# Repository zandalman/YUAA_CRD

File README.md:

## YUAA CRD

### Purpose
Our goal is to develop a cosmic ray detector (CRD) to serve as the scientific payload for the Yale Undergraduate Aerospace Association (YUAA) CubeSat. We will use cosmic rays to map the boundaries of the South Atlantic Anomaly (SAA).

### General CubeSat Info

CubeSats are miniature satellites composed of units consisting of 10 cm cubes. Yale was chosen by NASA as one of sixteen schools across the country whose CubeSat will be launched into space as auxiliary payloads on NASA missions. The Yale CubeSat consists of two 10 cm cube units. The CubeSat team is divided into several subteams: attitude determination and control (ADCS), radio, software, and cosmic ray detector (CRD). The CRD team interacts significantly with the ADCS and software teams. The software team writes C programs for our I2C components. We work with the ADCS team to coordinate mechanical design in the CubeSat, which is necessary due to the size constraints. The bulkiest part of the ADCS system is the gravity gradient boom (GGB), a measuring tape which spools out of the bottom of the CubeSat to generate restoring torques which stabilize the CubeSat’s orientation. The GGB includes a rotary encoder which provides feedback on the length of the GGB. The ADCS system also includes magnetorquers, electromagnets which generate torques using the Earth’s magnetic field, to maneuver the CubeSat.

### Background

#### Cosmic Rays

Cosmic rays are high-energy radiation originating from outside the solar system. About 99% of cosmic rays are bare atomic nuclei. 90% of these nuclei are protons (hydrogen nuclei), 9% are alpha particles (helium nuclei), and 1% are heavier elements. The other 1% of cosmic rays are beta particles (solitary electrons). Cosmic rays also include trace amounts of antiparticles like positrons and antiprotons. Sometimes, gamma rays (high-energy photons) are also considered cosmic rays. When cosmic rays enter the Earth’s atmosphere, they collide with atoms and molecules, producing a cascade of lighter particles known as secondary cosmic rays. Secondary cosmic rays are typically composed of neutrons, pions, kaons, and their antiparticles. Pions and kaons quickly decay into muons, neutrinos, and their antiparticles, which can be detected on Earth’s surface. The muon lifetime of 2.2 us should not be enough for muons to reach the surface of Earth, but due to relativistic time dilation their effective lifetime is longer in our reference frame. 1 Muons have similar properties to electrons but about 200 times the mass. Because muons are charged particles, we can use muons to test our detection circuitry before sending it into space.

#### Earth’s Magnetic Field

The Earth has a dipolar magnetic field generated by convection currents in Earth’s molten iron and nickel outer core. Energetic charged particles originating from solar wind and cosmic rays are captured by Earth’s magnetic field. Charged particles in a magnetic field move in helices about magnetic field lines. The concentration of charged particles peaks in two distinct regions above Earth’s surface, known as the inner and outer Van Allen belts. The gap between the Van Allen belts is caused by low frequency radio waves whose origin is still an area of active
research. 

There is a nonzero angle between the axis of Earth’s dipole magnetic field and its axis of rotation, causing the inner Van Allen belt to make its closest approach of about 2000 km to Earth’s surface above the South Atlantic. This region of enhanced radiation is called the South Atlantic Anomaly (SAA). The SAA dips low enough to intersect low Earth orbit. Satellites passing through the SAA are exposed to elevated levels of radiation for minutes at a time, leading to malfunctions, loss of observational time for telescopes, and danger to astronauts in the ISS.

#### Scintillators

A scintillator is a material that emits photons when excited by ionizing radiation. Commonly used scintillators often emit photons in the optical bands. There are many types of scintillators including organic crystals, organic liquids, plastic scintillators, inorganic crystals, gaseous scintillators, glasses, and perovskites. We use plastic scintillators, in which the primary fluorescent emitter, or fluor, is suspended in a base.

### Design

#### Mechanical

Using a band saw and a mill, we cut the scintillator down to a 1 cm cube due to size constraints in the CubeSat. Within the SAA, the particle flux is so high that our detection events would overlap. A layer of aluminum shielding around the scintillator reduces the number of events to the order of ~100 events per second. We calculated that a shielding thickness of 7 mm is sufficient. Because protons are more massive than electrons, cosmic ray protons typically have more energy than cosmic ray electrons, so the ratio of proton to electron events increases with shielding thickness.

The shielding is a 25 x 25 x 28 mm rectangular prism of aluminum with an 11 x 11 x 14 mm hole in the center for the scintillator cube and the SiPM. For ease of machining, the shielding is composed of 3 sections which are held together by 6-32 screws. At each of the bottom corners, the aluminum extends slightly further to give space for mounting holes.

When a charged particle passes through the scintillator, it deposits its kinetic energy into photons. We coat five sides of the scintillator with a reflective paint so that most photons eventually exit the scintillator at a single face. The non-coated face has a silicon photomultiplier (SiPM) which will detect the photons. The SiPM is optically coupled to the scintillator with optical jelly, an amorphous material with a prescribed refractive index. The SiPM is held fast against the scintillator by rubber stops which push against the inside faces of the shielding.

The SiPM is soldered onto a small printed circuit board (PCB) using a ball grid array (BGA). The PCB contains pads for the anode and cathode. Wires will be soldered directly to these pads and exit the shielding through a hole. The SiPM is AC coupled to a charge-sensitive preamplifier (preamp). The AC coupling circuit and the preamp come from an evaluation kit created by Ketek. The AC coupling circuit is mounted in a Thorlabs mount and the preamp is mounted in a rectangular aluminum box which acts as a Faraday cage, protecting it from radiation.

All of the circuitry minus the AC coupling circuit and preamp are contained on a custom 4-layer PCB, whose irregular shape is determined by the size constraints imposed by the GGB. This custom PCB will connect to the SiPM, AC coupling circuit, and preamp by a combination of wires and micro coax cables. Wires will be twisted together in pairs for extra stability.

#### Electrical

Our custom analog circuitry will count the number of cosmic ray detection events and classify them according to particle type. Our integrated circuit (IC) components communicate with the onboard computer (OBC) using I2C protocol, which requires clock and data lines. We have access to one set of clock and data lines from the OBC. An important aspect of I2C is that two devices cannot use the same clock and data lines if they have the same I2C address. Most IC chips which use I2C have address pins which allow you to set the I2C address to avoid overlap. We also have access to a 5 V power supply from the OBC.

As charged particles pass through the scintillator, their kinetic energy is converted into photons which activate cells on the SiPM. The SiPM is an avalanche photodiode, meaning that it consists of an array of photodiode cells. When a photon hits a cell, the cell emits electrons via the photoelectric effect. There is some “dead time” where the cell cannot detect another photon, so having an array of cells allows the SiPM to detect many photons in quick succession. The output pulse generated by the SiPM from a detection event is a sum of the signals generated by all of the photons produced by the particle passing through the scintillator.

The SiPM is AC coupled to a charge-sensitive preamp. In contrast to DC coupling, AC coupling rejects DC components of the signal, blocking any DC bias or offset voltage. AC coupling becomes important when the pulse frequency is sufficiently high that pulses overlap, resulting in a nonzero offset.

The preamp creates output pulses with an integrated voltage equal to the integrated current (i.e. charge) of the input pulses. The charge of the input pulses is physically meaningful because it is proportional to the total energy of the photons collected by the SiPM. The output pulses from the pre-amp look like a steep rising edge followed by an exponential decay with a time constant of ~100 ns. The height of the pulses ranges from 10 mV to 100 mV depending on the type of particle. Because all pulses have approximately the same shape, we can use the height of the pulse as a proxy for the integrated voltage. This pulse height analysis (PHA) is common in radiation detection.

If we had a larger budget, we would use a commercial multi-channel analyzer (MCA). However, instead we bin pulses by pulse height manually. Each pulse height bin is created with a system of three high-speed comparators. Two comparators act as upper and lower discriminators and a third comparator acts as an AND gate, only outputting high if the input voltage is between the two discriminators. The comparators are contained in IC chips with 4 comparators each. We have 7 bins total, so we need 21 comparators or 6 IC chips. The discriminator levels are set by 8 bit digital-to-analog converters (DACs). The DACs are contained in an IC chip with 8 DACs.

The outputs from the comparators are fed into real time clock (RTC) IC chips, which we program to count the number of pulses over the course of 5 min. There are 8 RTC chips, 7 for the pulse height bins and one for counting pulses from the rotary encoder for the GGB. The RTC chips only have one I2C address bin and therefore only two possible I2C addresses. We use an I2C multiplexer to mediate communication between the OBC and the RTC chips. The multiplexer has one input set of clock and data lines and four output sets of clock and data lines which each are used by 2 RTC chips, one with each possible I2C address.

We only have access to a 5 V power supply from the OBC. However, the preamp requires a 12 V power supply and the AC coupling circuit requires a 30 V bias voltage. We use boost converters to generate these voltages from the 5 V supply. All components draw negligible current, so there is no worry about drawing too much current.

The light output of the scintillator is temperature dependent and we don’t know exactly what the equilibrium temperature will be in the CubeSat once it is in space. Therefore, we use resistor temperature devices (RTDs) to monitor the temperature on our custom PCB and near the shielding.

The code for interfacing between the OBC and the I2C components of the circuit is managed by
the software subteam of the CubeSat and is available upon request.

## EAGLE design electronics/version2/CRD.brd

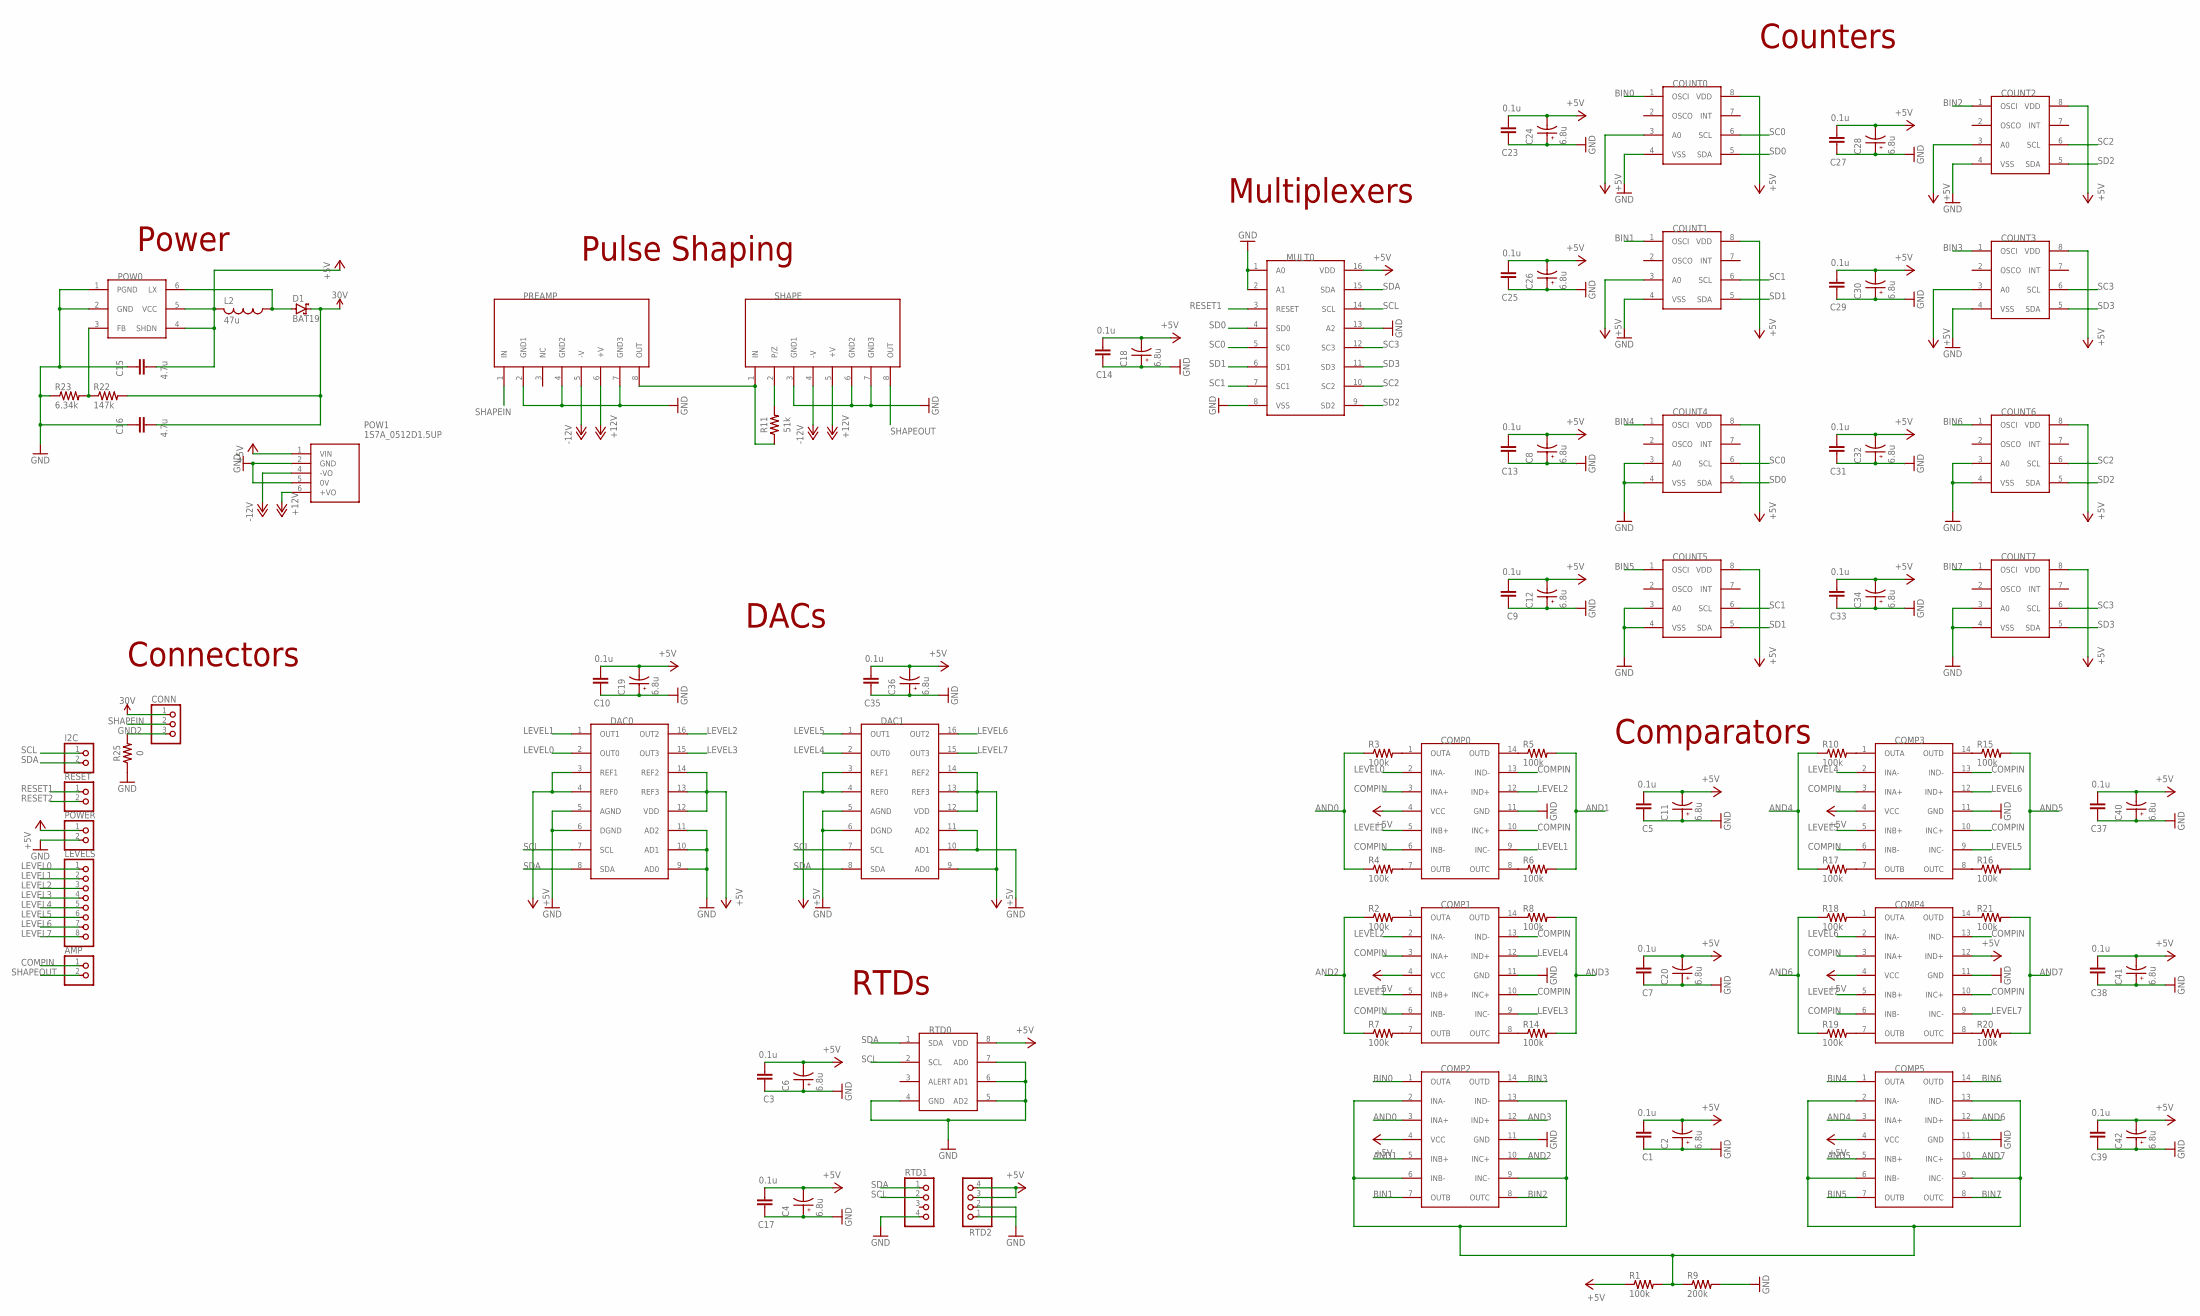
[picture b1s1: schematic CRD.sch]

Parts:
AMP: PINHD-1X2; 1X02
C1, C3, C5, C7, C9, C10, C13, C14, C17, C23, C25, C27, C29, C31, C33, C35, C37, C38, C39: 0.1u; CAP_1206
C2, C4, C6, C8, C11, C12, C18, C19, C20, C24, C26, C28, C30, C32, C34, C36, C40, C41, C42: 6.8u; CAPPRD150W45D400H700
C15, C16: 4.7u; CAP_1206
COMP0, COMP1, COMP2, COMP3, COMP4, COMP5: MAX9108ESD+; SOIC127P600X155-14N
CONN: PINHD-1X3; 1X03
COUNT0, COUNT1, COUNT2, COUNT3, COUNT4, COUNT5, COUNT6, COUNT7: PCF8583; SOIC127P1032X265-8N
D1: BAT19; DO35-10
DAC0, DAC1: MAX520BEWE+; SOIC127P1032X265-16N
I2C: PINHD-1X2; 1X02
L2: 47u; L1812
LEVELS: PINHD-1X8; 1X08
MULT0: PCA9546A; SOIC127P600X175-16N
POW0: MAX5025; SOT95P240X110-6N
POW1: 1S7A_0512D1.5UP; 1S7A_0505D15UP
POWER: PINHD-1X2; 1X02
PREAMP: CR-113; HDRV8W64P254_1X8_1016X508X838B
R1, R2, R3, R4, R5, R6, R7, R8, R10, R14, R15, R16, R17, R18, R19, R20, R21: 100k; RES_1206
R9: 200k; RES_1206
R11: 51k; RESAD1176W63L850D250B
R22: 147k; RES_1206
R23: 6.34k; RES_1206
R25: 0; RESAD724W46L381D178B
RESET: PINHD-1X2; 1X02
RTD0: NCT175DMR2G; SOP65P490X110-8N
RTD1, RTD2: PINHD-1X4; 1X04
SHAPE: CR-200; HDRV8W64P254_1X8_1016X508X838B

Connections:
+5V: C1.2, C2.N, C3.2, C4.N, C5.2, C6.N, C7.2, C8.N, C9.2, C10.2, C11.N, C12.N, C13.2, C14.2, C15.2, C17.2, C18.N, C19.N, C20.N, C23.2, C24.N, C25.2, C26.N, C27.2, C28.N, C29.2, C30.N, C31.2, C32.N, C33.2, C34.N, C35.2, C36.N, C37.2, C38.2, C39.2, C40.N, C41.N, C42.N, COMP0.4 (VCC), COMP1.4 (VCC), COMP2.4 (VCC), COMP3.4 (VCC), COMP4.4 (VCC), COMP4.12 (IND+), COMP5.4 (VCC), COUNT0.3 (A0), COUNT0.8 (VDD), COUNT1.3 (A0), COUNT1.8 (VDD), COUNT2.3 (A0), COUNT2.8 (VDD), COUNT3.3 (A0), COUNT3.8 (VDD), COUNT4.8 (VDD), COUNT5.8 (VDD), COUNT6.8 (VDD), COUNT7.8 (VDD), DAC0.3 (REF1), DAC0.4 (REF0), DAC0.12 (VDD), DAC0.13 (REF3), DAC0.14 (REF2), DAC1.3 (REF1), DAC1.4 (REF0), DAC1.9 (AD0), DAC1.12 (VDD), DAC1.13 (REF3), DAC1.14 (REF2), L2.2, MULT0.16 (VDD), POW0.4 (SHDN), POW0.5 (VCC), POW1.1 (VIN), POWER.1, R1.1, RTD0.8 (VDD), RTD2.3, RTD2.4
+12V: POW1.6 (+VO), PREAMP.6 (+V), SHAPE.5 (+V)
-12V: POW1.4 (-VO), PREAMP.5 (-V), SHAPE.4 (-V)
AND0: COMP2.3 (INA+), R3.1, R4.1
AND1: COMP2.5 (INB+), R5.2, R6.2
AND2: COMP2.10 (INC+), R2.1, R7.1
AND3: COMP2.12 (IND+), R8.2, R14.2
AND4: COMP5.3 (INA+), R10.1, R17.1
AND5: COMP5.5 (INB+), R15.2, R16.2
AND6: COMP5.12 (IND+), R18.1, R19.1
AND7: COMP5.10 (INC+), R20.2, R21.2
BIN0: COMP2.1 (OUTA), COUNT0.1 (OSCI)
BIN1: COMP2.7 (OUTB), COUNT1.1 (OSCI)
BIN2: COMP2.8 (OUTC), COUNT2.1 (OSCI)
BIN3: COMP2.14 (OUTD), COUNT3.1 (OSCI)
BIN4: COMP5.1 (OUTA), COUNT4.1 (OSCI)
BIN5: COMP5.7 (OUTB), COUNT5.1 (OSCI)
BIN6: COMP5.14 (OUTD), COUNT6.1 (OSCI)
BIN7: COMP5.8 (OUTC), COUNT7.1 (OSCI)
COMPIN: AMP.1, COMP0.3 (INA+), COMP0.6 (INB-), COMP0.10 (INC+), COMP0.13 (IND-), COMP1.3 (INA+), COMP1.6 (INB-), COMP1.10 (INC+), COMP1.13 (IND-), COMP3.3 (INA+), COMP3.6 (INB-), COMP3.10 (INC+), COMP3.13 (IND-), COMP4.3 (INA+), COMP4.6 (INB-), COMP4.10 (INC+), COMP4.13 (IND-)
GND: C1.1, C2.P, C3.1, C4.P, C5.1, C6.P, C7.1, C8.P, C9.1, C10.1, C11.P, C12.P, C13.1, C14.1, C15.1, C16.1, C17.1, C18.P, C19.P, C20.P, C23.1, C24.P, C25.1, C26.P, C27.1, C28.P, C29.1, C30.P, C31.1, C32.P, C33.1, C34.P, C35.1, C36.P, C37.1, C38.1, C39.1, C40.P, C41.P, C42.P, COMP0.11 (GND), COMP1.11 (GND), COMP2.11 (GND), COMP3.11 (GND), COMP4.11 (GND), COMP5.11 (GND), COUNT0.4 (VSS), COUNT1.4 (VSS), COUNT2.4 (VSS), COUNT3.4 (VSS), COUNT4.3 (A0), COUNT4.4 (VSS), COUNT5.3 (A0), COUNT5.4 (VSS), COUNT6.3 (A0), COUNT6.4 (VSS), COUNT7.3 (A0), COUNT7.4 (VSS), DAC0.5 (AGND), DAC0.6 (DGND), DAC0.9 (AD0), DAC0.10 (AD1), DAC0.11 (AD2), DAC1.5 (AGND), DAC1.6 (DGND), DAC1.10 (AD1), DAC1.11 (AD2), MULT0.1 (A0), MULT0.2 (A1), MULT0.8 (VSS), MULT0.13 (A2), POW0.1 (PGND), POW0.2 (GND), POW1.2 (GND), POW1.5 (0V), POWER.2, PREAMP.2 (GND1), PREAMP.4 (GND2), PREAMP.7 (GND3), R9.2, R23.1, R25.1, RTD0.4 (GND), RTD0.5 (AD2), RTD0.6 (AD1), RTD0.7 (AD0), RTD1.4, RTD2.2, SHAPE.3 (GND1), SHAPE.6 (GND2), SHAPE.7 (GND3)
GND2: CONN.3, R25.2
LEVEL0: COMP0.2 (INA-), DAC0.2 (OUT0), LEVELS.1
LEVEL1: COMP0.5 (INB+), COMP0.9 (INC-), DAC0.1 (OUT1), LEVELS.2
LEVEL2: COMP0.12 (IND+), COMP1.2 (INA-), DAC0.16 (OUT2), LEVELS.3
LEVEL3: COMP1.5 (INB+), COMP1.9 (INC-), DAC0.15 (OUT3), LEVELS.4
LEVEL4: COMP1.12 (IND+), COMP3.2 (INA-), DAC1.2 (OUT0), LEVELS.5
LEVEL5: COMP3.5 (INB+), COMP3.9 (INC-), DAC1.1 (OUT1), LEVELS.6
LEVEL6: COMP3.12 (IND+), COMP4.2 (INA-), DAC1.16 (OUT2), LEVELS.7
LEVEL7: COMP4.5 (INB+), COMP4.9 (INC-), DAC1.15 (OUT3), LEVELS.8
unnamed: COMP0.1 (OUTA), R3.2
unnamed: COMP0.7 (OUTB), R4.2
unnamed: COMP0.14 (OUTD), R5.1
unnamed: COMP0.8 (OUTC), R6.1
unnamed: COMP1.1 (OUTA), R2.2
unnamed: COMP1.7 (OUTB), R7.2
unnamed: COMP1.14 (OUTD), R8.1
unnamed: COMP1.8 (OUTC), R14.1
unnamed: PREAMP.8 (OUT), R11.1, SHAPE.1 (IN)
unnamed: R11.2, SHAPE.2 (P/Z)
unnamed: D1.A, L2.1, POW0.6 (LX)
unnamed: POW0.3 (FB), R22.1, R23.2
unnamed: COMP2.2 (INA-), COMP2.6 (INB-), COMP2.9 (INC-), COMP2.13 (IND-), COMP5.2 (INA-), COMP5.6 (INB-), COMP5.9 (INC-), COMP5.13 (IND-), R1.2, R9.1
unnamed: COMP3.1 (OUTA), R10.2
unnamed: COMP3.14 (OUTD), R15.1
unnamed: COMP3.8 (OUTC), R16.1
unnamed: COMP3.7 (OUTB), R17.2
unnamed: COMP4.1 (OUTA), R18.2
unnamed: COMP4.7 (OUTB), R19.2
unnamed: COMP4.8 (OUTC), R20.1
unnamed: COMP4.14 (OUTD), R21.1
RESET1: MULT0.3 (RESET), RESET.1
RESET2: RESET.2
SC0: COUNT0.6 (SCL), COUNT4.6 (SCL), MULT0.5 (SC0)
SC1: COUNT1.6 (SCL), COUNT5.6 (SCL), MULT0.7 (SC1)
SC2: COUNT2.6 (SCL), COUNT6.6 (SCL), MULT0.10 (SC2)
SC3: COUNT3.6 (SCL), COUNT7.6 (SCL), MULT0.12 (SC3)
SCL: DAC0.7 (SCL), DAC1.7 (SCL), I2C.1, MULT0.14 (SCL), RTD0.2 (SCL), RTD1.2
SD0: COUNT0.5 (SDA), COUNT4.5 (SDA), MULT0.4 (SD0)
SD1: COUNT1.5 (SDA), COUNT5.5 (SDA), MULT0.6 (SD1)
SD2: COUNT2.5 (SDA), COUNT6.5 (SDA), MULT0.9 (SD2)
SD3: COUNT3.5 (SDA), COUNT7.5 (SDA), MULT0.11 (SD3)
SDA: DAC0.8 (SDA), DAC1.8 (SDA), I2C.2, MULT0.15 (SDA), RTD0.1 (SDA), RTD1.1
SHAPEIN: CONN.2, PREAMP.1 (IN)
SHAPEOUT: AMP.2, SHAPE.8 (OUT)
VIN: C16.2, CONN.1, D1.C, R22.2

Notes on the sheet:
Power
Pulse Shaping
Connectors
Counters
RTDs
Multiplexers
DACs
Comparators

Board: 2 copper layers, 94 parts (0 on the bottom side), 65 nets, no tracks yet.

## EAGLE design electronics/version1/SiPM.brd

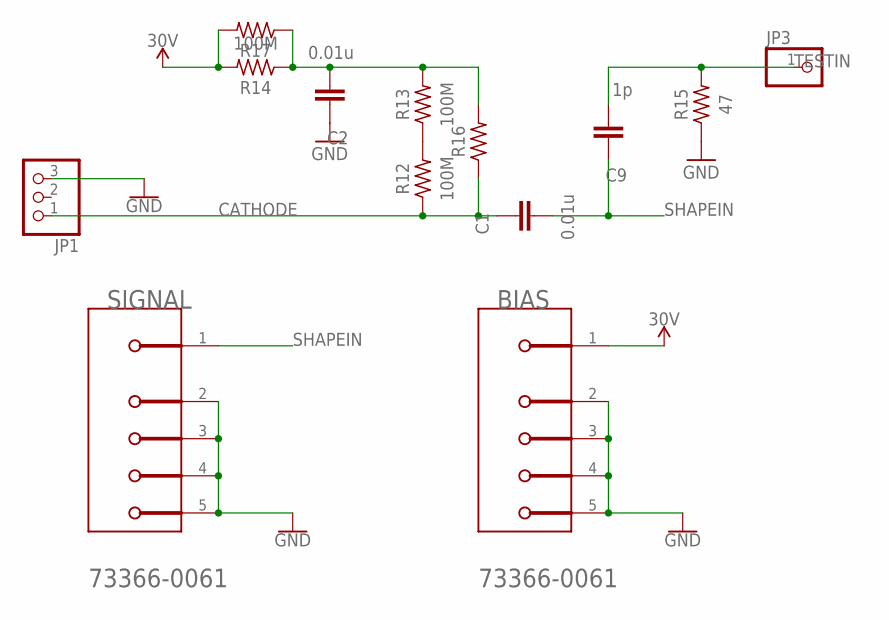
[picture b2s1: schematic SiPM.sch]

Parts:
BIAS: MOLEX_73366-0061MOLEX_73366-0061_0_0; MOLEX_73366-0061_0
C1, C2: 0.01u; CAP_1206
C9: 1p; CAP_1206
JP1: PINHD-1X3; 1X03
JP3: PINHD-1X1; 1X01
R12, R13, R14: 100M; RESAD1176W63L850D250B
R15: 47; RESAD1176W63L850D250B
R16, R17: R-US_AXIAL-11.7MM-PITCH; RESAD1176W63L850D250B
SIGNAL: MOLEX_73366-0061MOLEX_73366-0061_0_0; MOLEX_73366-0061_0

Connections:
CATHODE: C1.1, JP1.1, R12.1, R16.1
GND: BIAS.2 (MNT_1), BIAS.3 (MNT_2), BIAS.4 (MNT_3), BIAS.5 (MNT_4), C2.1, JP1.3, R15.1, SIGNAL.2 (MNT_1), SIGNAL.3 (MNT_2), SIGNAL.4 (MNT_3), SIGNAL.5 (MNT_4)
unnamed: R12.2, R13.1
unnamed: C2.2, R13.2, R14.1, R16.2, R17.1
SHAPEIN: C1.2, C9.1, SIGNAL.1
TESTIN: C9.2, JP3.1, R15.2
VIN: BIAS.1, R14.2, R17.2

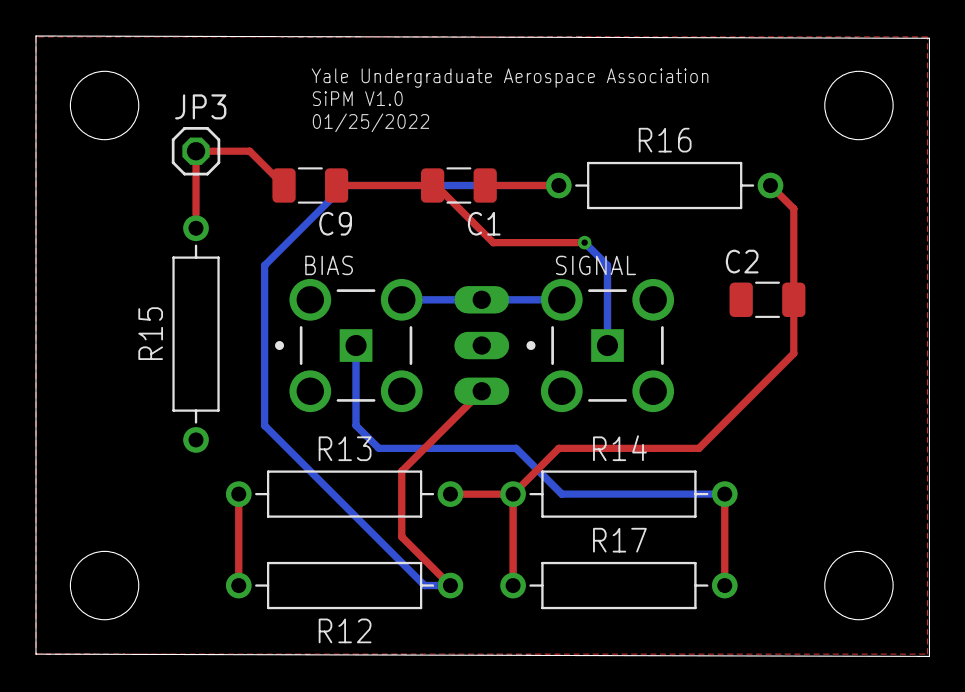
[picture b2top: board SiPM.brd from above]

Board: 2 copper layers, 49.6 x 34.5 mm, 13 parts (1 on the bottom side), 7 nets.

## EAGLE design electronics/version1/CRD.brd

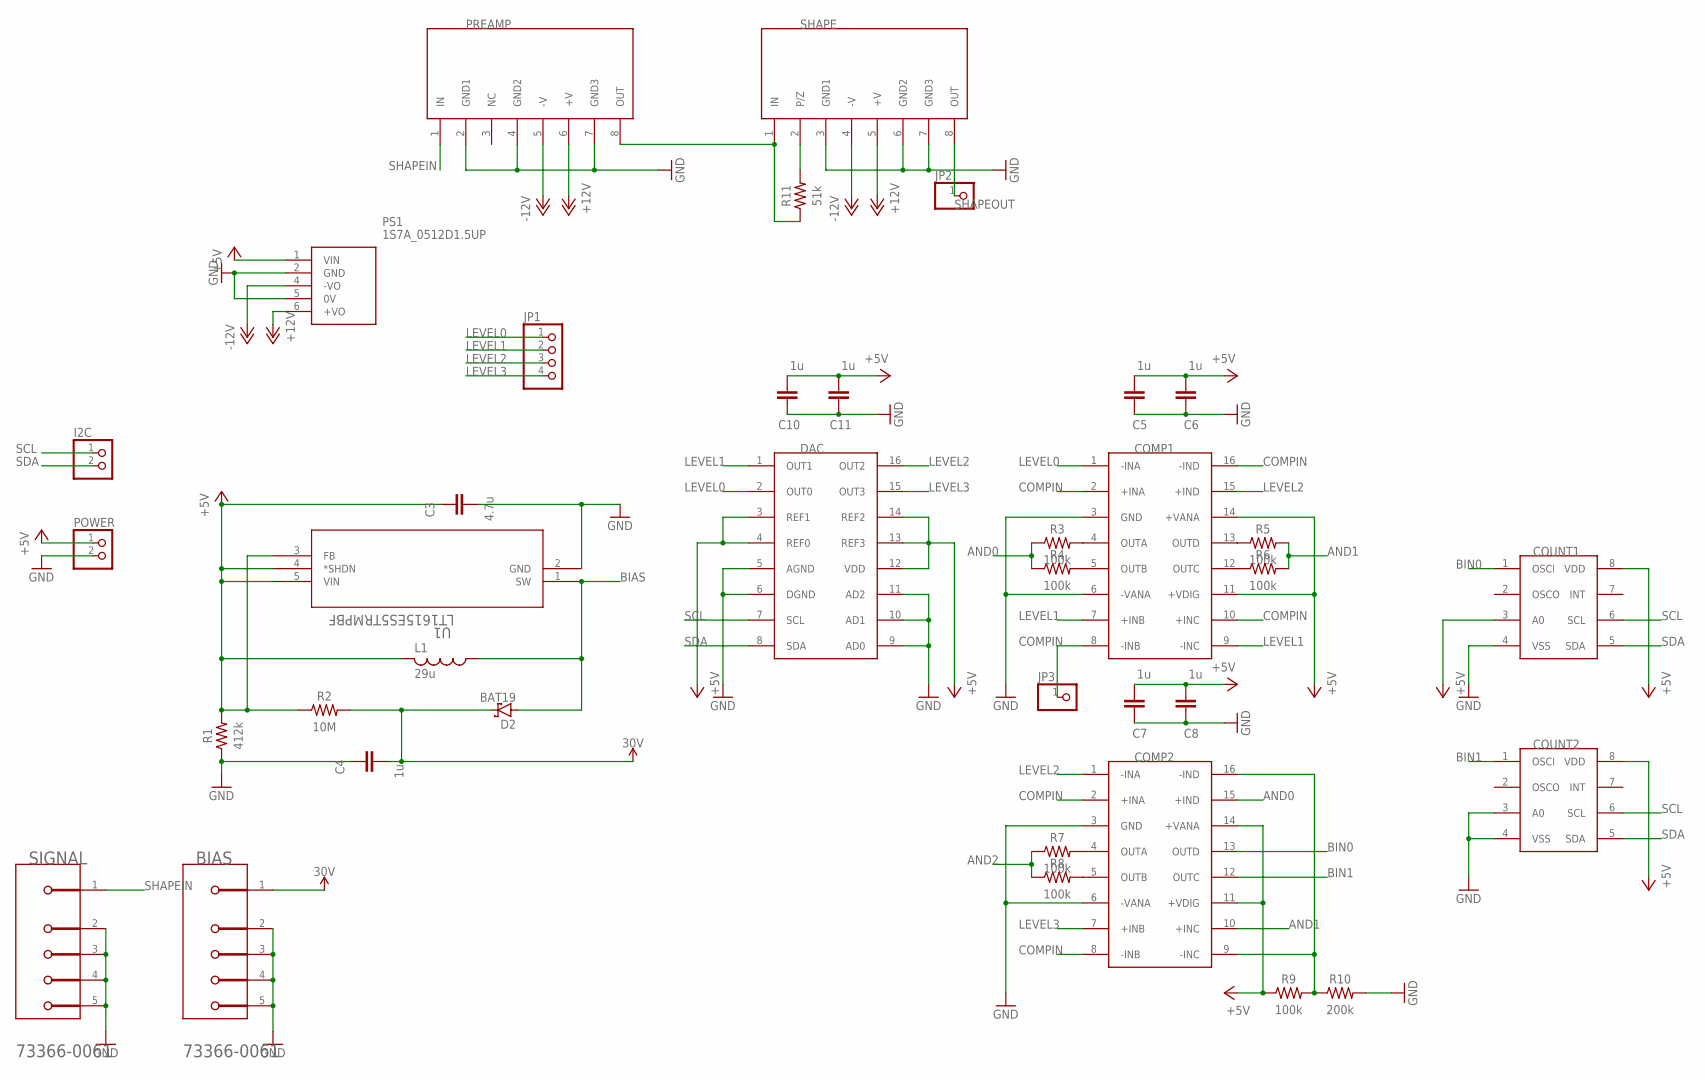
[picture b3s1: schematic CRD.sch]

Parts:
BIAS: MOLEX_73366-0061MOLEX_73366-0061_0_0; MOLEX_73366-0061_0
C3: 4.7u; CAP_1206
C4, C5, C6, C7, C8, C10, C11: 1u; CAP_1206
COMP1, COMP2: AD8564ARZ; SOIC127P1032X265-16N
COUNT1, COUNT2: PCF8583; SOIC127P1032X265-8N
D2: BAT19; DO35-10
DAC: MAX520BEWE+; SOIC127P1032X265-16N
I2C: PINHD-1X2; 1X02
JP1: PINHD-1X4; 1X04
JP2, JP3: PINHD-1X1; 1X01
L1: 29u; L1812
POWER: PINHD-1X2; 1X02
PREAMP: CR-113; HDRV8W64P254_1X8_1016X508X838B
PS1: 1S7A_0512D1.5UP; 1S7A_0505D15UP
R1: 412k; RESAD1176W63L850D250B
R2: 10M; RESAD1176W63L850D250B
R3, R4, R5, R6, R7, R8, R9: 100k; RESAD1176W63L850D250B
R10: 200k; RESAD1176W63L850D250B
R11: 51k; RESAD1176W63L850D250B
SHAPE: CR-200; HDRV8W64P254_1X8_1016X508X838B
SIGNAL: MOLEX_73366-0061MOLEX_73366-0061_0_0; MOLEX_73366-0061_0
U1: LT1615ES5TRMPBF; SOT-5_S

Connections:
+5V: C3.1, C5.2, C6.2, C7.2, C8.2, C10.2, C11.2, COMP1.11 (+VDIG), COMP1.14 (+VANA), COMP2.11 (+VDIG), COMP2.14 (+VANA), COUNT1.3 (A0), COUNT1.8 (VDD), COUNT2.8 (VDD), DAC.3 (REF1), DAC.4 (REF0), DAC.12 (VDD), DAC.13 (REF3), DAC.14 (REF2), L1.2, POWER.1, PS1.1 (VIN), R1.2, R2.1, R9.1, U1.3 (FB), U1.4 (*SHDN), U1.5 (VIN)
+12V: PREAMP.6 (+V), PS1.6 (+VO), SHAPE.5 (+V)
-12V: PREAMP.5 (-V), PS1.4 (-VO), SHAPE.4 (-V)
AND0: COMP2.15 (+IND), R3.1, R4.1
AND1: COMP2.10 (+INC), R5.2, R6.2
AND2: R7.1, R8.1
BIAS: D2.A, L1.1, U1.1 (SW)
BIN0: COMP2.13 (OUTD), COUNT1.1 (OSCI)
BIN1: COMP2.12 (OUTC), COUNT2.1 (OSCI)
COMPIN: COMP1.2 (+INA), COMP1.8 (-INB), COMP1.10 (+INC), COMP1.16 (-IND), COMP2.2 (+INA), COMP2.8 (-INB), JP3.1
GND: BIAS.2 (MNT_1), BIAS.3 (MNT_2), BIAS.4 (MNT_3), BIAS.5 (MNT_4), C3.2, C4.1, C5.1, C6.1, C7.1, C8.1, C10.1, C11.1, COMP1.3 (GND), COMP1.6 (-VANA), COMP2.3 (GND), COMP2.6 (-VANA), COUNT1.4 (VSS), COUNT2.3 (A0), COUNT2.4 (VSS), DAC.5 (AGND), DAC.6 (DGND), DAC.9 (AD0), DAC.10 (AD1), DAC.11 (AD2), POWER.2, PREAMP.2 (GND1), PREAMP.4 (GND2), PREAMP.7 (GND3), PS1.2 (GND), PS1.5 (0V), R1.1, R10.2, SHAPE.3 (GND1), SHAPE.6 (GND2), SHAPE.7 (GND3), SIGNAL.2 (MNT_1), SIGNAL.3 (MNT_2), SIGNAL.4 (MNT_3), SIGNAL.5 (MNT_4), U1.2 (GND)
LEVEL0: COMP1.1 (-INA), DAC.2 (OUT0), JP1.1
LEVEL1: COMP1.7 (+INB), COMP1.9 (-INC), DAC.1 (OUT1), JP1.2
LEVEL2: COMP1.15 (+IND), COMP2.1 (-INA), DAC.16 (OUT2), JP1.3
LEVEL3: COMP2.7 (+INB), DAC.15 (OUT3), JP1.4
unnamed: COMP1.4 (OUTA), R3.2
unnamed: COMP1.5 (OUTB), R4.2
unnamed: COMP1.13 (OUTD), R5.1
unnamed: COMP1.12 (OUTC), R6.1
unnamed: COMP2.4 (OUTA), R7.2
unnamed: COMP2.5 (OUTB), R8.2
unnamed: PREAMP.8 (OUT), R11.1, SHAPE.1 (IN)
unnamed: R11.2, SHAPE.2 (P/Z)
unnamed: COMP2.9 (-INC), COMP2.16 (-IND), R9.2, R10.1
SCL: COUNT1.6 (SCL), COUNT2.6 (SCL), DAC.7 (SCL), I2C.1
SDA: COUNT1.5 (SDA), COUNT2.5 (SDA), DAC.8 (SDA), I2C.2
SHAPEIN: PREAMP.1 (IN), SIGNAL.1
SHAPEOUT: JP2.1, SHAPE.8 (OUT)
VIN: BIAS.1, C4.2, D2.C, R2.2

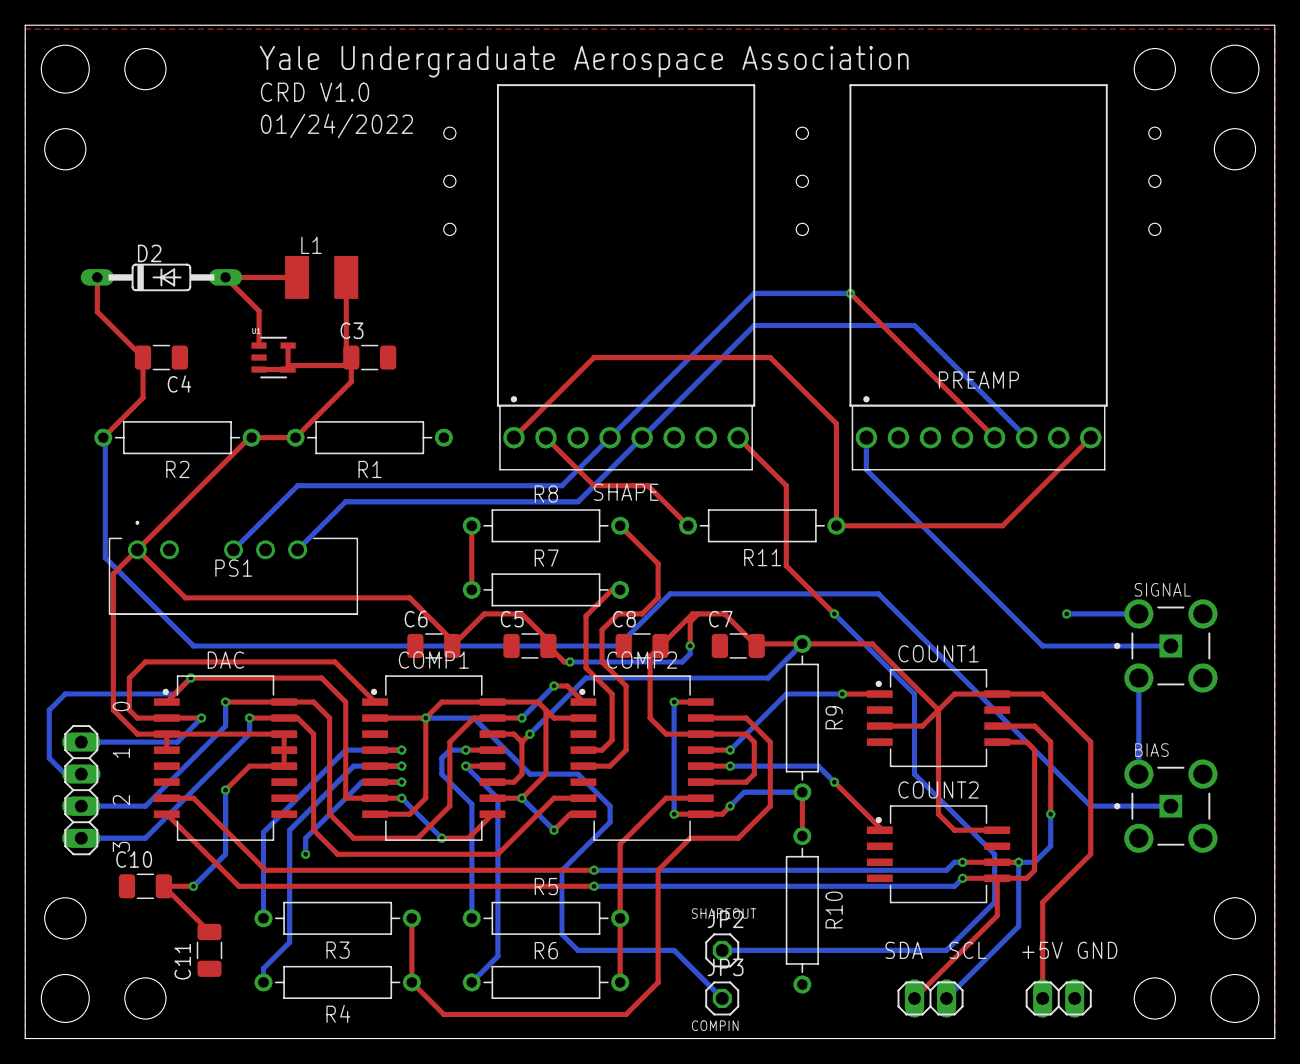
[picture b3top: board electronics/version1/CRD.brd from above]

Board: 2 copper layers, 99.0 x 80.3 mm, 37 parts (0 on the bottom side), 29 nets.

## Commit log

2022-02-11 Add files via upload
    ADCS + some magnetometer code
2022-02-14 Doing some reorganization
2022-09-25 Updated repo with all PCB versions
2022-09-25 added example
2022-10-15 analysis of energy loss in sheilding
2023-01-28 added test.txt to show EE team about github
2023-01-28 deleted the file

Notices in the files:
parts and their libraries:
SparkFun-PowerSymbols: Licensing: Creative Commons ShareAlike 4.0 International - https://creativecommons.org/licenses/by-sa/4.0
